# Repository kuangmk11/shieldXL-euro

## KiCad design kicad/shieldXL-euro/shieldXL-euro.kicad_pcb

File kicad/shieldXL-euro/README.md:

# shieldXL-euro

A 20 HP Eurorack module from okyeron / denki-oto's
[shieldXL](https://github.com/okyeron/shieldXL), itself a remix of monome's
[norns shield](https://github.com/monome/norns-shield). GPL-3.0, as both are.

The original KiCad project, `../ShieldXL-M-20230615`, is left as it is, so
upstream fixes still merge. This copy changes only what Eurorack needs.

## What changes

| | shieldXL | shieldXL-euro |
|---|---|---|
| audio | 4 x 6.35 mm, line level | 4 x 3.5 mm (Thonkiconn); TL074 stages scale 10 Vpp modular to the codec and back |
| MIDI | PJ-320B TRS jacks, Type A/B slide switch | PJ366ST stereo Thonkiconns; A/B by two shunts on a 2 x 3 header (J123): top row Type A, bottom row Type B |
| Pi power | the Pi's own USB | USB-C on the panel, through a polyfuse and TVS onto +5V. The Pi never runs from the rack, so a rack power cycle cannot catch it mid-write |
| rack power | - | 10-pin header, ±12 V for the op-amps only, reverse protected |
| USB host | the Pi's own ports | three USB-A sockets on the panel, each cabled from a Pi port |
| headphones | - | none: the outputs go to the rack |

Display, keys, encoders and the MIDI circuit are shieldXL's. The codec is a
TI PCM3060 in place of shieldXL's CS4270, which Cirrus ended in 2023 (last buy
Dec 2023): same place, same wires, swapped by `tools/swap_codec_pcm3060.py`
(pin map there). Still the I2S clock master off the 12.288 MHz crystal; its
ADC follows the DAC's clocks, which takes Moirae's copy of the kernel driver
(`../../software/pcm3060-moirae`) and the overlay in
`../../install/boot/overlays`.

## Levels

- **In:** a 69.8k / 30.1k divider (100k in, x0.301) into a follower, then
  shieldXL's divider re-set for the PCM3060's 10k input, 1.27k / 4.53k
  (x0.71 loaded). 13.3 Vpp at the jack reaches the ADC's full scale,
  0.6 x 4.75 V = 2.85 Vpp; hotter signals clip in the codec, not the op-amp.
- **Out:** the DAC runs single-ended, 0.8 x 4.75 V = 3.8 Vpp full scale,
  through shieldXL's output filter into a non-inverting stage, gain 2.62
  (16.2k / 10k), then 1k: about 10 Vpp at the jack.
- **Phase:** both stages are non-inverting.

## Pi power

The Pi is powered through the 40-pin header, not its own USB-C / micro-USB
port, so nothing plugs into that port and no right-angle adapter is needed.
J108 on the panel feeds F101 and D103 onto `+5V`, and `+5V` is header pins 2
and 4 (X1), as on shieldXL.

- **Protection.** Header power bypasses the Pi's own input protection; F101
  and D103 stand in for it.
- **Voltage drop.** The Pi flags undervoltage at about 4.63 V. A 3 A 1812
  polyfuse drops around 0.1 V at 2-2.5 A, before the cable and connector.
  With a marginal supply that can trip the warning; a lower-resistance fuse
  or an eFuse would leave more margin.
- **Two supplies.** Plugging the Pi's own power port in while J108 is live
  ties the two supplies together. It can't be reached in a rack; on the
  bench, use one or the other. An ideal-diode controller on J108 would make
  it safe.
- **Pi 5.** Powered from the header it cannot negotiate USB PD, and limits
  its USB ports to 600 mA in total unless `usb_max_current_enable=1` is set
  in `config.txt`. That matters with three USB-A sockets on the panel.
  shieldXL's images are for the Pi 4.

## Files

    shieldXL-euro.kicad_sch          root: the two shield sheets and eurorack.kicad_sch
    norns-shield-210330_1/_2.kicad_sch   shieldXL's sheets, desktop I/O removed
    eurorack.kicad_sch               the Eurorack I/O - generated, do not edit by hand
    tools/strip_shield_io.py         removes the 6.35 mm jacks, PJ-320Bs and slide switch
    tools/make_eurorack_sheet.py     writes eurorack.kicad_sch and hooks it into the root
    tools/schlib.py                  pin positions and wire checks for the scripts

The two shield sheets are joined to the Eurorack sheet by global labels:

- **Audio:** `IN_L_LINE`, `IN_R_LINE`, `OUT_L_LINE`, `OUT_R_LINE`.
- **MIDI:** `MIDI_OUT_SRC`, `MIDI_OUT_SNK`, `MIDI_IN_TIP`, `MIDI_IN_RING`.
- **Power and grounds:** the shield's own `+5V`, `GND` and `AGND` symbols.

The panel layout is in the Missing Mile Modular repo
(`ShieldXL Euro/tools/build_panel.py`). The board will be placed to its holes.

## Checked

- **Netlist:**
  - Removing the desktop I/O changed no other connection. Every shield net
    keeps exactly its pins, less the removed parts'.
  - The new sheet's cross-sheet nets land on the parts named above.
- **ERC:** 34 findings, against the original's 47 (`kicad-cli sch erc`,
  KiCad 10; unchanged by the Corone jacks and headers).
  - 16 of the original's are gone with the parts that caused them.
  - 4 are new: two net-name aliases (`TIP1_5` / `RING1_4` now also carry the
    global `MIDI_OUT_*` names), and AGND / GND "not driven". That is the
    same kind of finding the original has on its Eagle-era power pins.
  - The rest are inherited from the original.

## Not done yet

- **The board.** The outline is drawn (`tools/make_outline.py`, run with
  KiCad's Python): 98 x 108 mm behind the 20 HP panel, with the panel, the
  display and the Pi traced on User.1-4. The board is routed and DRC clean;
  ground stitching is `tools/stitch_ground.py`, net classes
  `tools/set_netclasses.py`. The panel parts and the Pi are
  placed and locked by `tools/place_panel_parts.py`; the panel, artwork
  included, is on User.1 (back artwork on User.5). The
  stack, front to back: panel, display on standoffs behind the window, main
  board, Pi 4 on the back, upside down as on MONOFA (extra-tall header,
  about 20 mm standoffs). The 20 mm, main board's back to the Pi's PCB, lets
  the Pi's USB stacks (16 mm) clear the SMD parts under them by 2 mm; it is
  modelled (`tools/set_3d_models.py`, on X1) as an 8.5 mm 2x20 socket on the
  board with a 2x20 stacking header in it, then the Pi's 2.5 mm header base.
- **The Pi lies landscape, header along the top**, behind the display and
  clear of the controls. That is why the module is 20 HP: 85 mm of Pi, its
  ports, a USB adapter and the microSD card come to about 96 mm, more than
  18 HP's 91.3. Two small adapter boards plug into its USB stacks and
  carry the four ports to J112 / J113 (boxed 2 x 4) on 8-way IDC ribbons
  (`../usb-adapter`). Only its two holes by the header are screwed down
  (footprint `MMM:RASPI_BOARD_B+_UPPER_HOLES`): the other two land on K1's
  and E2's pins, so those corners stand on 3D-printed feet fixed to the Pi,
  drawn on User.3. Keys are C&K D6R00 (`MMM:SW_CK_D6R`). The
  panel is drawn in the Missing Mile Modular repo and named Moirae there.
- **Corone (crow).** Two CV inputs and four CV outputs, the six jacks in the
  panel's CORONE outline. A daughterboard running monome's own crow
  firmware, on one 2 x 10 header on the back of the main board, lower half,
  below the Pi; USB to norns through the Pi's fourth port. Spec and
  schematic in `../corone/`. The main board's side is in the Eurorack sheet:
  J115-J120 jacks, J121 header, J122 ii; its USB comes through J113.
- **A vertical USB-C receptacle.** KiCad's library has none. J108 has no
  footprint until a part is chosen.
- **Keys.** SW1-SW3 are still shieldXL's Choc / MX key footprints; the
  panel is drawn for 9.3 mm round caps (C&K D6 style).
- **USB-A cable headers.** USB on a 4-pin JST PH is fine for full speed;
  keep the cables short. The plugs into the Pi's own USB-A ports stick out
  sideways and cost depth and side clearance behind the panel. Plan the
  layout around a small adapter board or flex with low-profile right-angle
  plugs, carried back to the main board.

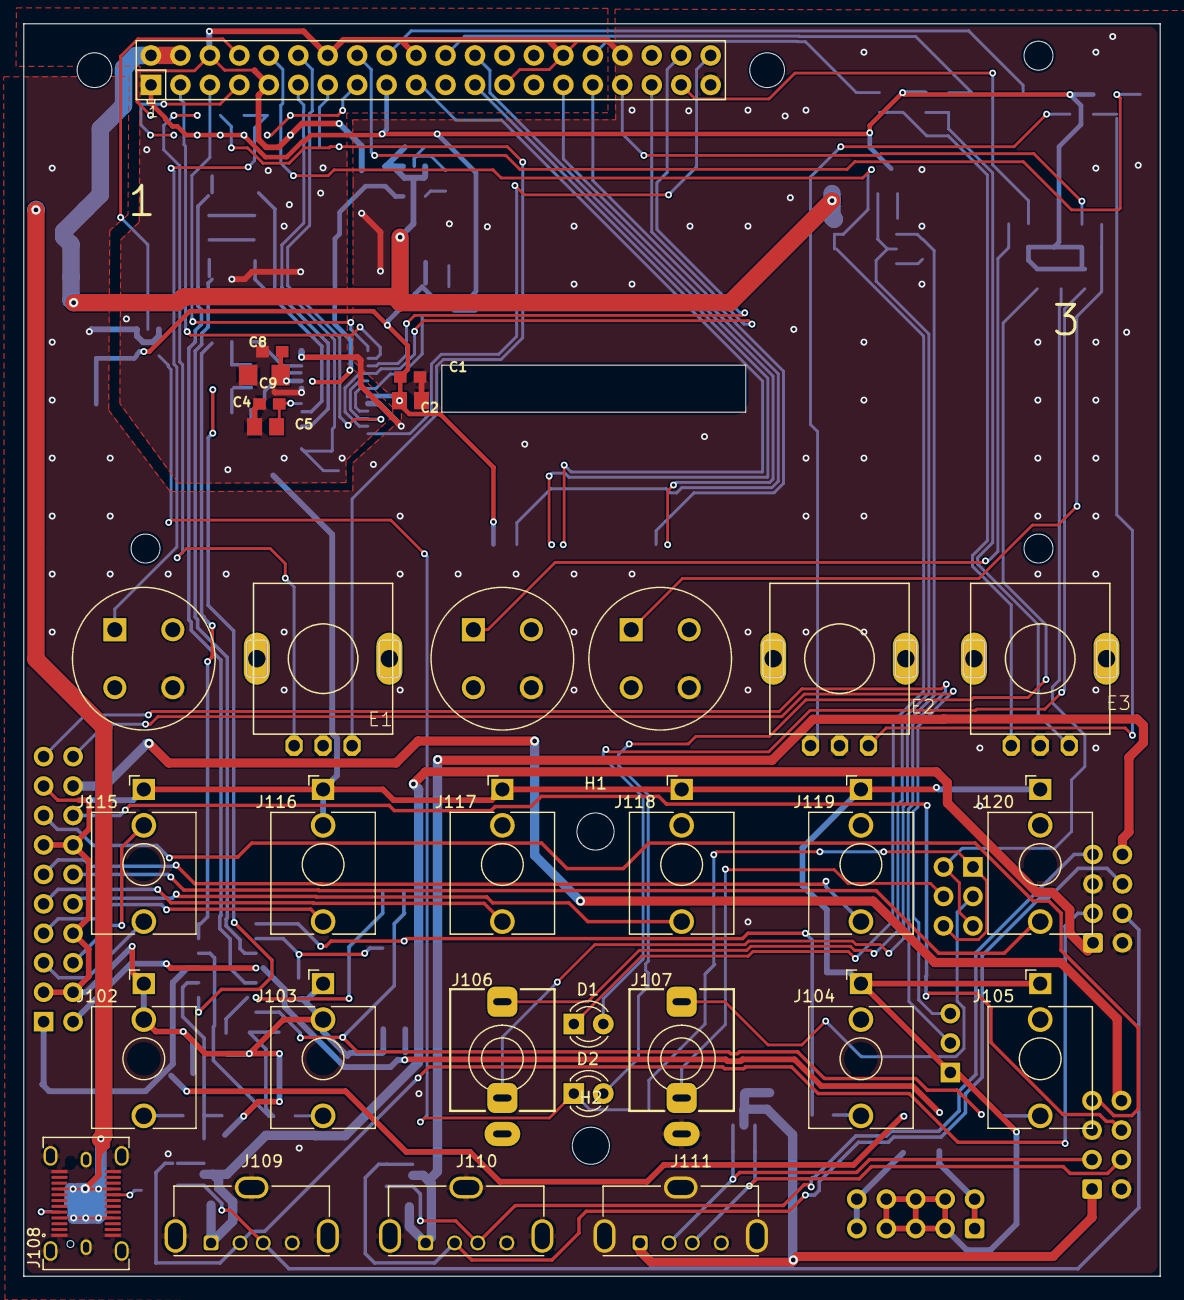
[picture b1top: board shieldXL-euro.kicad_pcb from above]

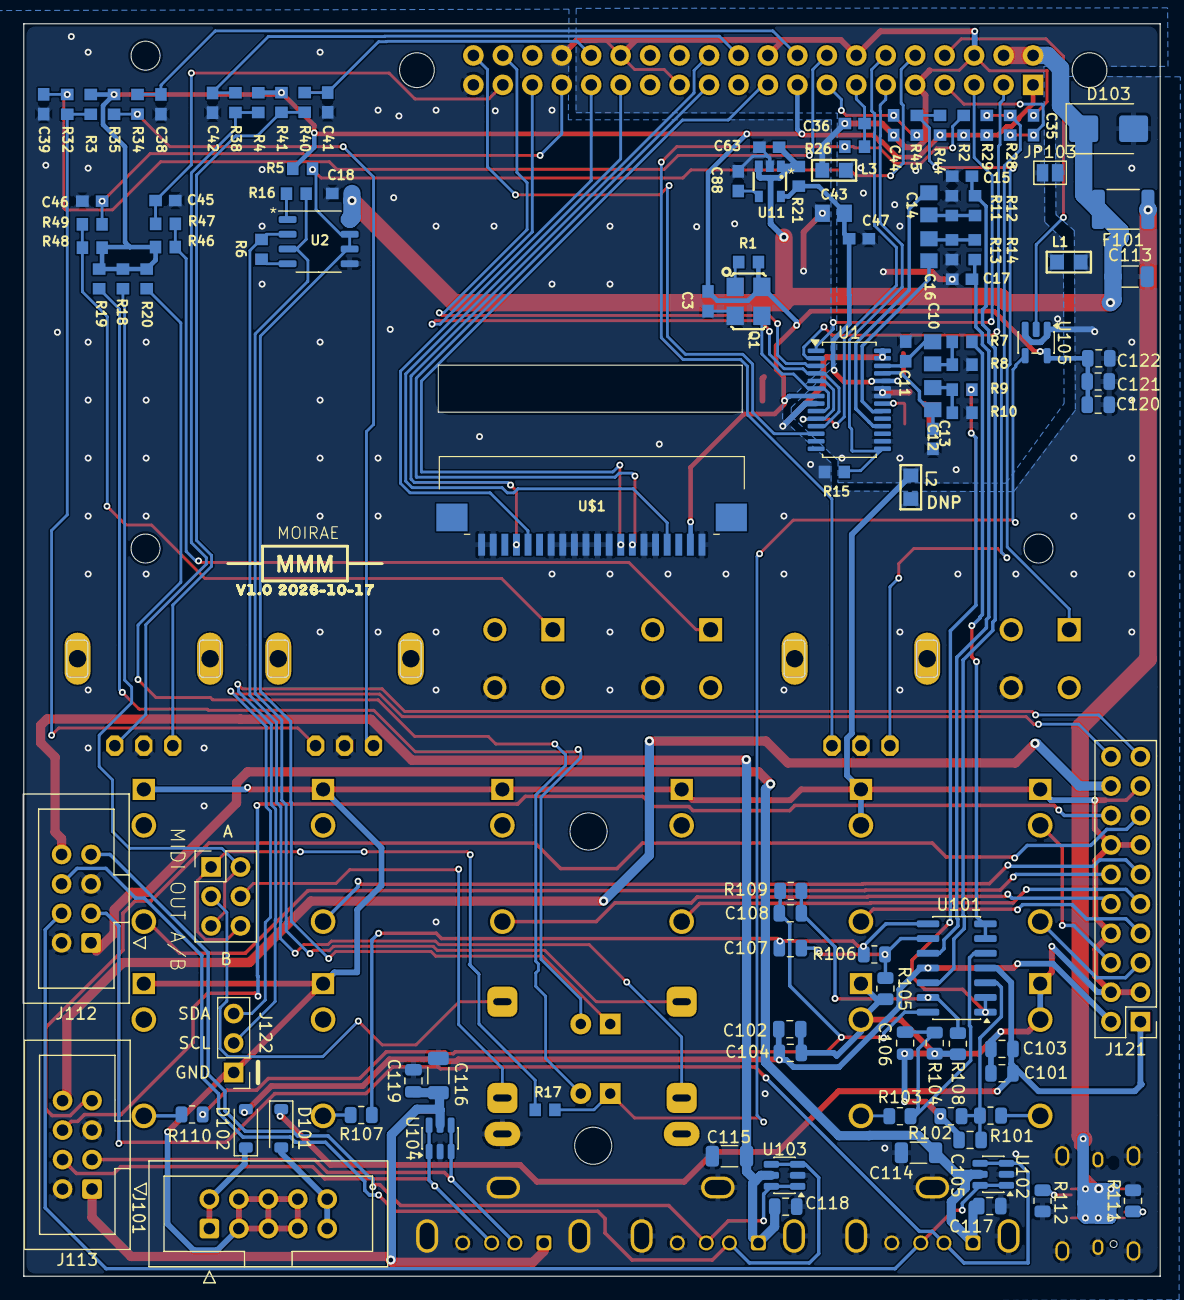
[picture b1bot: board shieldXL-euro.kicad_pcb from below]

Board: 2 copper layers, 98.0 x 108.0 mm, 151 parts (113 on the bottom side), 102 nets.

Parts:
C1, C4, C8, C18, C47, C63: 100n; C0603
C2, C5, C10, C12, C43: 10u; C0805
C3, C35, C36, C38, C39, C41, C42, C44, C45, C46, C88: 10n; C0603
C9: 47u; C1206
C11, C13: 220p COG; C0603
C14, C16: 3.3u; C0805
C15, C17: 2700p COG; C0603
C101, C102: 10u 25V; C_0805_2012Metric
C103, C104, C117, C118, C119, C120, C122: 100n; C_0805_2012Metric
C105, C106, C107, C108: 100p; C_0805_2012Metric
C113: 47u; C_1206_3216Metric
C114, C115, C116: 47u 10V; C_1206_3216Metric
C121: 10u; C_0805_2012Metric
COR1: Corone; Corone_Daughterboard
D1, D2: RED 3mm; LED_3mm_PadsAC
D101, D102: B5819W; D_SOD-123
D103: SMBJ5.0CA; D_SMB
DS1: NHD-2.7-12864WDW3-M; Display_NHD-2.7-12864WDW3
E1, E2, E3: ENC; PEC11RN
F101: 3A hold; Fuse_1812_4532Metric
H1, H2: M3; MountingHole_3.2mm_M3
J101: Eurorack power; IDC-Header_2x05_P2.54mm_Vertical
J102: IN L; Jack_3.5mm_QingPu_WQP-PJ398SM_Vertical_CircularHoles
J103: IN R; Jack_3.5mm_QingPu_WQP-PJ398SM_Vertical_CircularHoles
J104: OUT L; Jack_3.5mm_QingPu_WQP-PJ398SM_Vertical_CircularHoles
J105: OUT R; Jack_3.5mm_QingPu_WQP-PJ398SM_Vertical_CircularHoles
J106: MIDI IN; Jack_3.5mm_QingPu_WQP-PJ366ST_Vertical
J107: MIDI OUT; Jack_3.5mm_QingPu_WQP-PJ366ST_Vertical
J108: DX07S024WJ1R350; USB_C_Receptacle_JAE_DX07S024WJ1R350
J109: USB 1; USB_A_Molex_105057_Vertical
J110: USB 2; USB_A_Molex_105057_Vertical
J111: USB 3; USB_A_Molex_105057_Vertical
J112: Pi USB, inner stack; IDC-Header_2x04_P2.54mm_Vertical
J113: Pi USB, outer stack; IDC-Header_2x04_P2.54mm_Vertical
J115: CORONE I/1; Jack_3.5mm_QingPu_WQP-PJ398SM_Vertical_CircularHoles
J116: CORONE I/2; Jack_3.5mm_QingPu_WQP-PJ398SM_Vertical_CircularHoles
J117: CORONE O/1; Jack_3.5mm_QingPu_WQP-PJ398SM_Vertical_CircularHoles
J118: CORONE O/2; Jack_3.5mm_QingPu_WQP-PJ398SM_Vertical_CircularHoles
J119: CORONE O/3; Jack_3.5mm_QingPu_WQP-PJ398SM_Vertical_CircularHoles
J120: CORONE O/4; Jack_3.5mm_QingPu_WQP-PJ398SM_Vertical_CircularHoles
J121: Corone; PinHeader_2x10_P2.54mm_Vertical
J122: ii; PinHeader_1x03_P2.54mm_Vertical
J123: MIDI OUT A/B; PinHeader_2x03_P2.54mm_Vertical
JP103: AGND-GND; SolderJumper-2_P1.3mm_Open_Pad1.0x1.5mm
L1, L2: DNP; L0805
L3: FERRITE; L0805
PNL1: Moirae panel; Panel_Moirae
Q1: ASFL1-12.288MHZ-LCS-T; ASF
R1, R2, R3, R4, R11, R13, R15, R26, R28, R29, R32, R34, R35, R38, R40, R41, R44, R45, R46, R47, R48, R49: 10k; R0603
R5, R19, R20: 470Ω; R0603
R6, R16: 220Ω; R0603
R7, R9: 1.27k; R0603
R8, R10: 4.53k; R0603
R12, R14: 590; R0603
R17: 100Ω; R0603
R18: 47Ω; R0603
R21: DNP; R0603
R101, R103: 69.8k; R_0805_2012Metric
R102, R104: 30.1k; R_0805_2012Metric
R105, R108: 10k; R_0805_2012Metric
R106, R109: 16.2k; R_0805_2012Metric
R107, R110: 1k; R_0805_2012Metric
R111, R112: 5.1k; R_0805_2012Metric
SW1, SW2, SW3: D6R00 F1 LFS; SW_CK_D6R
U1: PCM3060PW; TSSOP-28_4.4x9.7mm_P0.65mm
U2: HCPL-0631-500E; SSOP-8_3.9x5.05mm_P1.27mm
U11: TPS793475DBVR; SSOP5
U101: TL074; SOIC-14_3.9x8.7mm_P1.27mm
U102, U103, U104: USBLC6-2SC6; SOT-23-6
U105: 74LVC1G125; SOT-23-5
U$1: FPC1M20P-B310; F-FPC1M20P-B310
USBA1, USBA2: USB adapter; USB_Adapter_Pi
X1: RASPI_BOARD_B+#_E3; RASPI_BOARD_B+_UPPER_HOLES

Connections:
+3V3: C1.1, C2.1, C3.1, C120.1, C121.1, C122.1, Q1.4 (VCC), R1.1, R2.2, R3.2, R4.2, R5.2, R18.2, R19.2, R20.2, R29.2, R35.2, R41.2, R44.1, R46.1, R48.1, U1.7 (VDD), U105.5 (VCC), U$1.2 (VDD), X1.1 (3V3A), X1.17 (3V3B)
+5V: C18.2, C63.1, C113.1, D103.1 (A1), F101.2, R21.1, U2.8 (VCC), U11.1 (IN), U11.3 (EN), X1.2 (5V0A), X1.4 (5V0B)
+12V: C101.1, C103.1, D101.1 (K), J121.1, U101.4 (V+)
-12V: C102.2, C104.2, D102.2 (A), J121.2, U101.11 (V-)
/eurorack/+12V_IN: D101.2 (A), J101.9, J101.10
/eurorack/-12V_IN: D102.1 (K), J101.1, J101.2
/eurorack/CC1: J108.A5 (CC1), R111.1
/eurorack/CC2: J108.B5 (CC2), R112.1
/eurorack/CRW_IN1: J115.T, J121.5
/eurorack/CRW_IN1_NORM: J115.TN, J121.6
/eurorack/CRW_IN2: J116.T, J121.7
/eurorack/CRW_OUT1: J117.T, J121.9
/eurorack/CRW_OUT2: J118.T, J121.10
/eurorack/CRW_OUT3: J119.T, J121.11
/eurorack/CRW_OUT4: J120.T, J121.12
/eurorack/CRW_USB_DM: J113.6, J121.16
/eurorack/CRW_USB_DP: J113.7, J121.15
/eurorack/CRW_USB_VBUS: J113.8, J121.18
/eurorack/II_SCL: J121.19, J122.2
/eurorack/II_SDA: J121.20, J122.3
/eurorack/INL_DIV: C105.1, R101.2, R102.1, U101.3 (+)
/eurorack/INR_DIV: C106.1, R103.2, R104.1, U101.5 (+)
/eurorack/IN_L_JACK: J102.T, R101.1
/eurorack/IN_R_JACK: J103.T, R103.1
/eurorack/MIDI_OUT_R: J107.R, J123.4
/eurorack/MIDI_OUT_T: J107.T, J123.3
/eurorack/OUTL_AMP: C107.2, R106.2, R107.1, U101.8
/eurorack/OUTL_FB: C107.1, R105.1, R106.1, U101.9 (-)
/eurorack/OUTR_AMP: C108.2, R109.2, R110.1, U101.14
/eurorack/OUTR_FB: C108.1, R108.1, R109.1, U101.13 (-)
/eurorack/OUT_L_JACK: J104.T, R107.2
/eurorack/OUT_R_JACK: J105.T, R110.2
/eurorack/USB1_DM: J109.2 (D-), J112.3, U102.3 (I/O2), U102.4 (I/O2)
/eurorack/USB1_DP: J109.3 (D+), J112.4, U102.1 (I/O1), U102.6 (I/O1)
/eurorack/USB1_VBUS: C114.1, C117.1, J109.1 (VBUS), J112.1, U102.5 (VBUS)
/eurorack/USB2_DM: J110.2 (D-), J112.6, U103.3 (I/O2), U103.4 (I/O2)
/eurorack/USB2_DP: J110.3 (D+), J112.7, U103.1 (I/O1), U103.6 (I/O1)
/eurorack/USB2_VBUS: C115.1, C118.1, J110.1 (VBUS), J112.8, U103.5 (VBUS)
/eurorack/USB3_DM: J111.2 (D-), J113.3, U104.3 (I/O2), U104.4 (I/O2)
/eurorack/USB3_DP: J111.3 (D+), J113.4, U104.1 (I/O1), U104.6 (I/O1)
/eurorack/USB3_VBUS: C116.1, C119.1, J111.1 (VBUS), J113.1, U104.5 (VBUS)
/eurorack/VBUS_C: F101.1, J108.A4 (VBUS), J108.A9 (VBUS), J108.B4 (VBUS), J108.B9 (VBUS)
/norns-shield-210330_1/A5V: C8.1, C9.1, C43.1, C47.1, R21.2, U1.24 (VCC), U11.6 (OUT)
/norns-shield-210330_1/INA: C10.1, C11.1, U1.26 (VINR)
/norns-shield-210330_1/INB: C12.1, C13.1, U1.25 (VINL)
/norns-shield-210330_1/LRCK: U1.4 (LRCK1), U1.11 (LRCK2), X1.35 (GPIO19)
/norns-shield-210330_1/MCLK: Q1.3 (FO), U1.6 (SCKI1), U1.9 (SCKI2)
/norns-shield-210330_1/OUTA: C14.1, U1.18 (VOUTR+)
/norns-shield-210330_1/OUTB: C16.1, U1.20 (VOUTL+)
/norns-shield-210330_1/R-CODEC: R15.1, U1.15 (~RST), X1.11 (GPIO17)
/norns-shield-210330_1/SCL: U1.1 (MC/SCL), X1.5 (SCL)
/norns-shield-210330_1/SCLK: U1.5 (BCK1), U1.10 (BCK2), X1.12 (GPIO18)
/norns-shield-210330_1/SDA: U1.2 (MD/SDA), X1.3 (SDA)
/norns-shield-210330_1/SDIN: U1.12 (DIN), X1.40 (GPIO21)
/norns-shield-210330_1/SDOUT: U1.3 (DOUT), X1.38 (GPIO20)
A1: C35.1, R28.2, X1.7 (GPIO04)
A2: C38.1, R34.2, X1.18 (GPIO24)
A3: C41.1, R40.2, X1.32 (GPIO12)
AGND: C4.2, C5.2, C8.2, C9.2, C11.2, C13.2, C15.2, C17.2, C47.2, C101.2, C102.1, C103.2, C104.1, C105.2, C106.2, J101.3, J101.4, J101.5, J101.6, J101.7, J101.8, J102.S, J102.TN, J103.S, J103.TN, J104.S, J105.S, J115.S, J116.S, J116.TN, J117.S, J118.S, J119.S, J120.S, J121.3, J121.4, J121.8, J121.13, J121.14, J121.17, J122.1, JP103.1 (A), L1.1, L2.1, L3.1, R8.2, R10.2, R11.2, R13.2, R102.2, R104.2, R105.2, R108.2, U1.16 (SGND), U1.22 (AGND2), U1.23 (AGND1)
B1: C36.1, R26.2, X1.13 (GPIO27)
B2: C39.1, R32.2, X1.16 (GPIO23)
B3: C42.1, R38.2, X1.22 (GPIO25)
CE0: U$1.17 (/CS), X1.24 (SPI_CE0)
GND: C1.2, C2.2, C3.2, C18.1, C35.2, C36.2, C38.2, C39.2, C41.2, C42.2, C43.2, C44.2, C45.2, C46.2, C63.2, C88.2, C113.2, C114.2, C115.2, C116.2, C117.2, C118.2, C119.2, C120.2, C121.2, C122.2, D103.2 (A2), E1.GND, E2.GND, E3.GND, J107.S, J108.A1 (GND), J108.A12 (GND), J108.B1 (GND), J108.B12 (GND), J108.SH (SHIELD), J109.4 (GND), J109.SH (Shield), J110.4 (GND), J110.SH (Shield), J111.4 (GND), J111.SH (Shield), J112.2, J112.5, J113.2, J113.5, JP103.2 (B), L1.2, L2.2, L3.2, Q1.2 (GND), R15.2, R111.2, R112.2, SW1.SW2 (PIN-2), SW2.SW2 (PIN-2), SW3.SW2 (PIN-2), U1.8 (DGND), U1.27 (MS/ADR), U1.28 (MODE), U2.5 (GND), U11.2 (GND), U102.2 (GND), U103.2 (GND), U104.2 (GND), U105.1, U105.3 (GND), U$1.1 (VSS), U$1.5 (R/W), U$1.6 (E), U$1.9 (DB2), U$1.10 (DB3), U$1.11 (DB4), U$1.12 (DB5), U$1.13 (DB6), U$1.14 (DB7), U$1.19 (BS1), U$1.20 (BS0), X1.6 (GND_A), X1.9 (GND_B), X1.14 (GND_C), X1.20 (GND_D), X1.25 (GND_E), X1.30 (GND_F), X1.34 (GND_G), X1.39 (GND_H)
IN_L_LINE: R9.2, U101.1, U101.2 (-)
IN_R_LINE: R7.2, U101.6 (-), U101.7
K1: C44.1, R45.2, X1.15 (GPIO22)
K2: C45.1, R47.2, X1.37 (GPIO26)
K3: C46.1, R49.2, X1.33 (GPIO13)
MIDI_IN_RING: J106.R, R6.1, U2.2 (CATHODE_1)
MIDI_IN_TIP: J106.T, R16.1, U2.3 (CATHODE_2)
MIDI_OUT_SNK: J123.1, J123.6, R17.1
MIDI_OUT_SRC: J123.2, J123.5, R18.1
MIDI_RX: D1.C, R5.1, U2.6 (VO2), U2.7 (VO1), X1.10 (RXD)
MIDI_TX: U105.2, X1.8 (TXD)
MIDI_TX_BUF: D2.C, R17.2, U105.4
MOSI: U$1.8 (SDIN), X1.19 (SPI_MOSI)
unnamed: C10.2, R7.1, R8.1
unnamed: C12.2, R9.1, R10.1
unnamed: C14.2, R11.1, R12.1
unnamed: C16.2, R13.1, R14.1
unnamed: D1.A, R19.1
unnamed: D2.A, R20.1
unnamed: E1.A, R28.1, R29.1
unnamed: E1.B, R2.1, R26.1
unnamed: E2.A, R34.1, R35.1
unnamed: E2.B, R3.1, R32.1
unnamed: E3.A, R40.1, R41.1
unnamed: E3.B, R4.1, R38.1
unnamed: Q1.1 (OE), R1.2
unnamed: R44.2, R45.1, SW1.SW1 (PIN-1)
unnamed: R46.2, R47.1, SW2.SW1 (PIN-1)
unnamed: R48.2, R49.1, SW3.SW1 (PIN-1)
unnamed: C4.1, C5.1, U1.21 (VCOM)
unnamed: R16.2, U2.1 (ANODE_1)
unnamed: R6.2, U2.4 (ANODE_2)
unnamed: C88.1, U11.4 (NR)
OUT_L_LINE: C17.1, R14.2, U101.10 (+)
OUT_R_LINE: C15.1, R12.2, U101.12 (+)
O_DC: U$1.4 (D/C), X1.29 (GPIO05)
O_RESET: U$1.16 (/RES), X1.31 (GPIO06)
SCK: U$1.7 (SCLK), X1.23 (SPI_SCLK)

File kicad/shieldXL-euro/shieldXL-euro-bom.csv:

Refs,Qty,Value,Footprint,Manufacturer,MPN,DigiKey PN,DigiKey PN status,Notes
"C1,C4,C8,C18,C47,C63",6,100n,C0603,Samsung,CL10B104KB8NNNC,1276-1000-1-ND,verified,
"C2,C5,C10,C12,C43",5,10u,C0805,Samsung,CL21A106KAYNNNE,1276-2891-1-ND,verified,
"C3,C35,C36,C38,C39,C41,C42,C44-C46,C88",11,10n,C0603,Samsung,CL10B103KB8NNWC,1276-1923-1-ND,verified,
C9,1,47u,C1206,Samsung,CL31A476MPHNNNE,1276-3063-1-ND,pattern - confirm,
"C11,C13",2,220p COG,C0603,Samsung,CL10C221JB8NNNC,,,
"C14,C16",2,3.3u,C0805,Samsung,CL21A335KAQNNNE,,,
"C15,C17",2,2700p COG,C0603,Murata,GRM1885C1H272JA01D,,,
"C101,C102,C121",3,10u 25V / 10u,C_0805_2012Metric,Samsung,CL21A106KAYNNNE,1276-2891-1-ND,verified,
"C103,C104,C117-C120,C122",7,100n,C_0805_2012Metric,Samsung,CL21B104KBCNNNC,1276-1003-1-ND,verified,
C105-C108,4,100p,C_0805_2012Metric,Samsung,CL21C101JBANNNC,1276-1014-1-ND,pattern - confirm,
"C113,C114-C116",4,47u / 47u 10V,C_1206_3216Metric,Samsung,CL31A476MPHNNNE,1276-3063-1-ND,pattern - confirm,
"D1,D2",2,RED 3mm,LED_3mm_PadsAC,Lite-On,LTL-4211N,160-1956-ND,verified,
"D101,D102",2,B5819W,D_SOD-123,EVVO,B5819W,5272-B5819WCT-ND,verified,
D103,1,SMBJ5.0CA,D_SMB,Littelfuse,SMBJ5.0CA,SMBJ5.0CALFCT-ND,verified,
E1-E3,3,ENC,PEC11RN,Bourns,PEC11R-4215F-N0024,PEC11R-4215F-N0024-ND,verified,
F101,1,3A hold,Fuse_1812_4532Metric,Littelfuse,1812L300MR,F4162CT-ND,verified,
J101,1,Eurorack power,IDC-Header_2x05_P2.54mm_Vertical,Wurth,61201021621,,,boxed 2x5; any 2.54 mm shrouded header
"J102,J103,J104,J105,J115,J116,J117,J118,J119,J120",10,IN L / IN R / OUT L / OUT R / CORONE I/1 / CORONE I/2 / CORONE O/1 / CORONE O/2 / CORONE O/3 / CORONE O/4,Jack_3.5mm_QingPu_WQP-PJ398SM_Vertical_CircularHoles,Thonk,Thonkiconn PJ398SM,,,not at Digi-Key: Thonk / Tayda
"J106,J107",2,MIDI IN / MIDI OUT,Jack_3.5mm_QingPu_WQP-PJ366ST_Vertical,Thonk,Thonkiconn PJ366ST (stereo),,,not at Digi-Key: Thonk
J108,1,DX07S024WJ1R350,USB_C_Receptacle_JAE_DX07S024WJ1R350,JAE,DX07S024WJ1R350,670-2949-1-ND,verified,backorder at Digi-Key when checked
"J109,J110,J111",3,USB 1 / USB 2 / USB 3,USB_A_Molex_105057_Vertical,Molex,1050570001,WM8672-ND,verified,
"J112,J113",2,"Pi USB, inner stack / Pi USB, outer stack",IDC-Header_2x04_P2.54mm_Vertical,Wurth,61200821621,,,"boxed 2x4, through hole - check the Wurth variant is THT"
J121,1,Corone,PinHeader_2x10_P2.54mm_Vertical,Sullins,PRPC010DAAN-RC,,,
J122,1,ii,PinHeader_1x03_P2.54mm_Vertical,Sullins,PRPC003SAAN-RC,S1011EC-03-ND,pattern - confirm,
J123,1,MIDI OUT A/B,PinHeader_2x03_P2.54mm_Vertical,Sullins,PRPC003DAAN-RC,,,
L3,1,FERRITE,L0805,Murata,BLM21PG221SN1D,490-1054-1-ND,verified,
Q1,1,ASFL1-12.288MHZ-LCS-T,ASF,Abracon,ASFL1-12.288MHZ-L-T,535-10810-1-ND,verified,schematic value LCS-T; Digi-Key stocks the -L-T (same 12.288 MHz 3.3 V ASFL1)
"R1-R4,R11,R13,R15,R26,R28,R29,R32,R34,R35,R38,R40,R41,R44-R49",22,10k,R0603,Yageo,RC0603FR-0710KL,311-10.0KHRCT-ND,pattern - confirm,
"R5,R19,R20",3,470Ω,R0603,Yageo,RC0603FR-07470RL,311-470HRCT-ND,pattern - confirm,
"R6,R16",2,220Ω,R0603,Yageo,RC0603FR-07220RL,311-220HRCT-ND,pattern - confirm,
"R7,R9",2,1.27k,R0603,Yageo,RC0603FR-071K27L,311-1.27KHRCT-ND,pattern - confirm,
"R8,R10",2,4.53k,R0603,Yageo,RC0603FR-074K53L,311-4.53KHRCT-ND,pattern - confirm,
"R12,R14",2,590,R0603,Yageo,RC0603FR-07590RL,311-590HRCT-ND,pattern - confirm,
R17,1,100Ω,R0603,Yageo,RC0603FR-07100RL,311-100HRCT-ND,pattern - confirm,
R18,1,47Ω,R0603,Yageo,RC0603FR-0747RL,311-47.0HRCT-ND,pattern - confirm,
"R101,R103",2,69.8k,R_0805_2012Metric,Yageo,RC0805FR-0769K8L,311-69.8KCRCT-ND,pattern - confirm,
"R102,R104",2,30.1k,R_0805_2012Metric,Yageo,RC0805FR-0730K1L,311-30.1KCRCT-ND,pattern - confirm,
"R105,R108",2,10k,R_0805_2012Metric,Yageo,RC0805FR-0710KL,311-10.0KCRCT-ND,pattern - confirm,
"R106,R109",2,16.2k,R_0805_2012Metric,Yageo,RC0805FR-0716K2L,311-16.2KCRCT-ND,pattern - confirm,
"R107,R110",2,1k,R_0805_2012Metric,Yageo,RC0805FR-071KL,311-1.00KCRCT-ND,pattern - confirm,
"R111,R112",2,5.1k,R_0805_2012Metric,Yageo,RC0805FR-075K1L,311-5.10KCRCT-ND,pattern - confirm,
SW1-SW3,3,D6R00 F1 LFS,SW_CK_D6R,C&K,D6R00 F1 LFS,108-D6R00F1LFS-ND,verified,white cap
U$1,1,FPC1M20P-B310,F-FPC1M20P-B310,Ckmtw,F-FPC1M20P-B310,,,not at Digi-Key: LCSC C132515
U1,1,PCM3060PW,TSSOP-28_4.4x9.7mm_P0.65mm,TI,PCM3060PW,296-21668-5-ND,verified,replaces the EOL CS4270; needs software/pcm3060-moirae
U2,1,HCPL-0631-500E,SSOP-8_3.9x5.05mm_P1.27mm,Broadcom,HCPL-0631-500E,516-1580-1-ND,verified,
U11,1,TPS793475DBVR,SSOP5,TI,TPS793475DBVR,296-TPS793475DBVRCT-ND,verified,
U101,1,TL074,SOIC-14_3.9x8.7mm_P1.27mm,TI,TL074CDR,296-1283-1-ND,verified,
U102-U104,3,USBLC6-2SC6,SOT-23-6,ST,USBLC6-2SC6,497-5235-1-ND,verified,
U105,1,74LVC1G125,SOT-23-5,TI,SN74LVC1G125DBVR,296-11603-1-ND,verified,
X1,1,RASPI_BOARD_B+#_E3,RASPI_BOARD_B+_UPPER_HOLES,Raspberry Pi,Raspberry Pi 4 Model B,,,plus a 2x20 stacking header for the 20 mm stack
(J123),2,shunt,-,Sullins,SPC02SYAN,S9001-ND,verified,MIDI out A/B: both on the top row = Type A
(X1),1,2x20 stacking header,-,,"2x20 2.54 mm stacking header, long pins",,,Pi 20 mm behind the board on the 8.5 mm socket; not in the schematic
(COR1),2,M3 standoff 11 mm F-F,-,,M3 x 11 mm female-female standoff,,,"Corone to main board, H1/H2; plus 4 M3 x 6 screws"
"(J112,J113)",2,"8-way ribbon, IDC both ends",-,,8-way 1.27 mm ribbon + 2x4 IDC sockets,,,to the two USB adapters; red stripe to pin 1 at both ends

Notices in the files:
parts and their libraries:
Imported from clacktronics/AudioJacks (github.com/clacktronics/AudioJacks, rev 14a8886, MIT, (c) 2021 Barwise - see doc/AudioJacks-LICENSE.txt).
